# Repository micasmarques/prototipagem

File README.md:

# Prototipagem

Repositório da disciplina de Tecnicas de Prototipagem, com as atividades e o projeto da disciplina.

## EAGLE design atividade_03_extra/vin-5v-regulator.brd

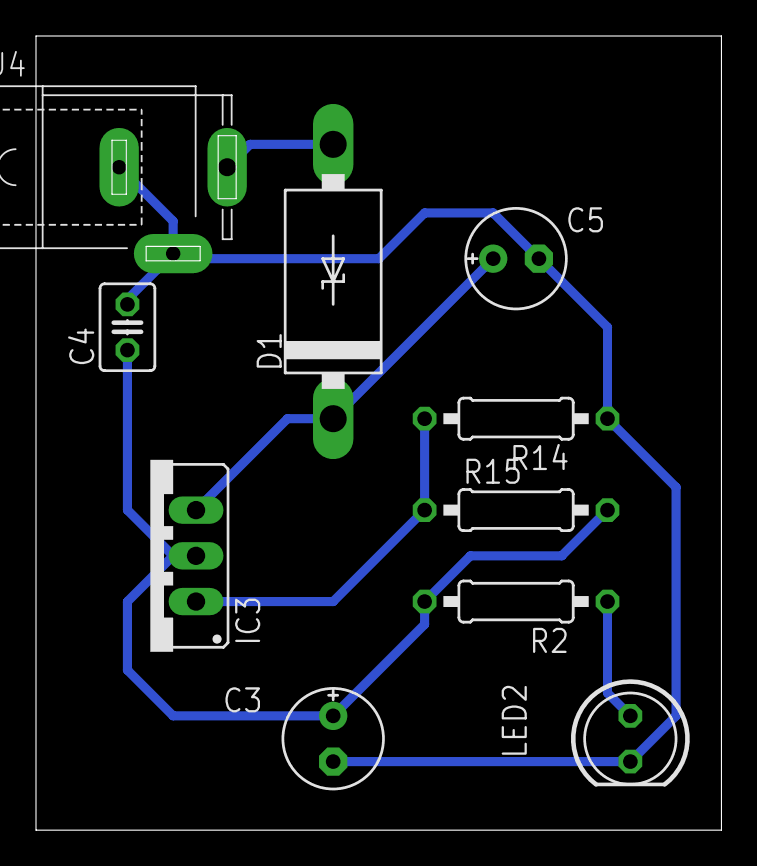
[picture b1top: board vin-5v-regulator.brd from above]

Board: 2 copper layers, 38.1 x 44.1 mm, 10 parts (0 on the bottom side), 6 nets.

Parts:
C3: 10uF; E2,5-6E
C4: 100nF; C025-030X050
C5: 47uF; E2,5-6E
D1: 1N5908; C4111-15
IC3: LM317; 317TS
J4: SPC4077
LED2: VERDE; LED5MM
R2: 1K; 0207/10
R14: 715; 0207/10
R15: 240; 0207/10

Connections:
+5V: C3.+, C4.1, IC3.2, R2.2, R15.2
GND: C3.-, C4.2, C5.-, J4.1, J4.2, LED2.K, R14.1
unnamed: D1.A, J4.3
unnamed: C5.+, D1.C, IC3.3
unnamed: IC3.1, R14.2, R15.1
unnamed: LED2.A, R2.1

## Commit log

2021-12-06 Create a
2021-12-14 ajeitando
2021-12-23 atividade 4 feita
2022-03-21 Eixo Z finalizado
    Eixo Z finalizado, projeto concluido, e adicionado logo da equipe
